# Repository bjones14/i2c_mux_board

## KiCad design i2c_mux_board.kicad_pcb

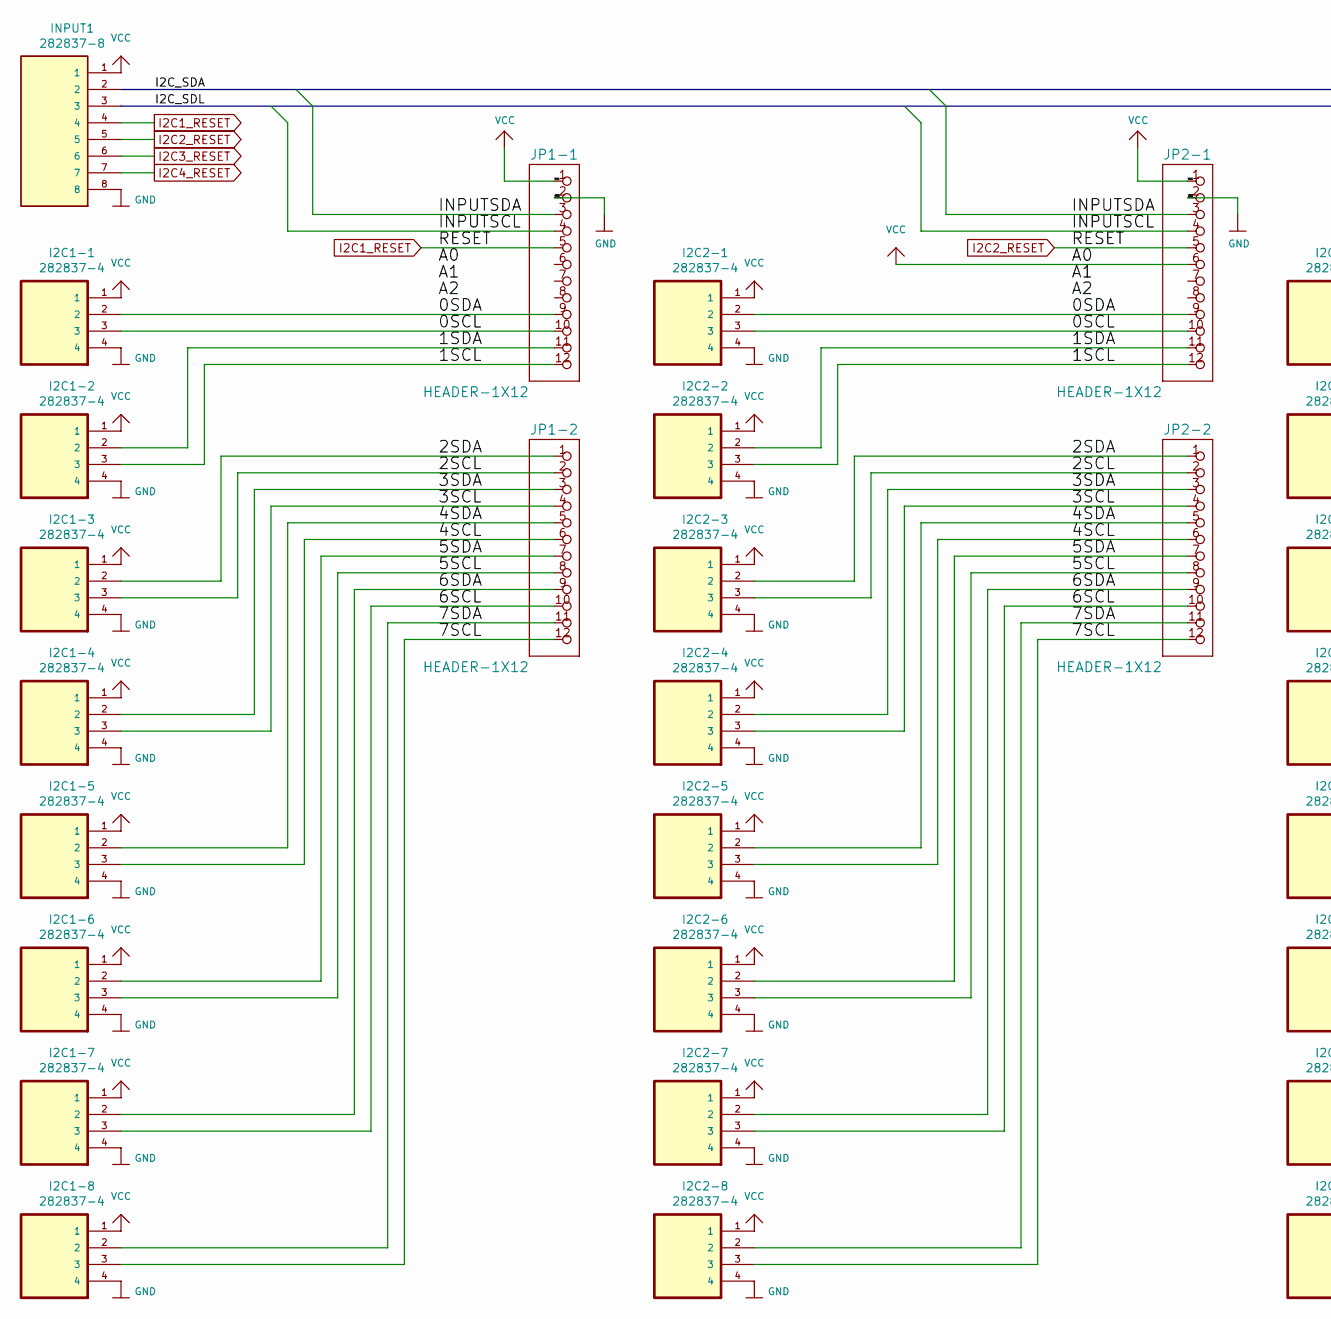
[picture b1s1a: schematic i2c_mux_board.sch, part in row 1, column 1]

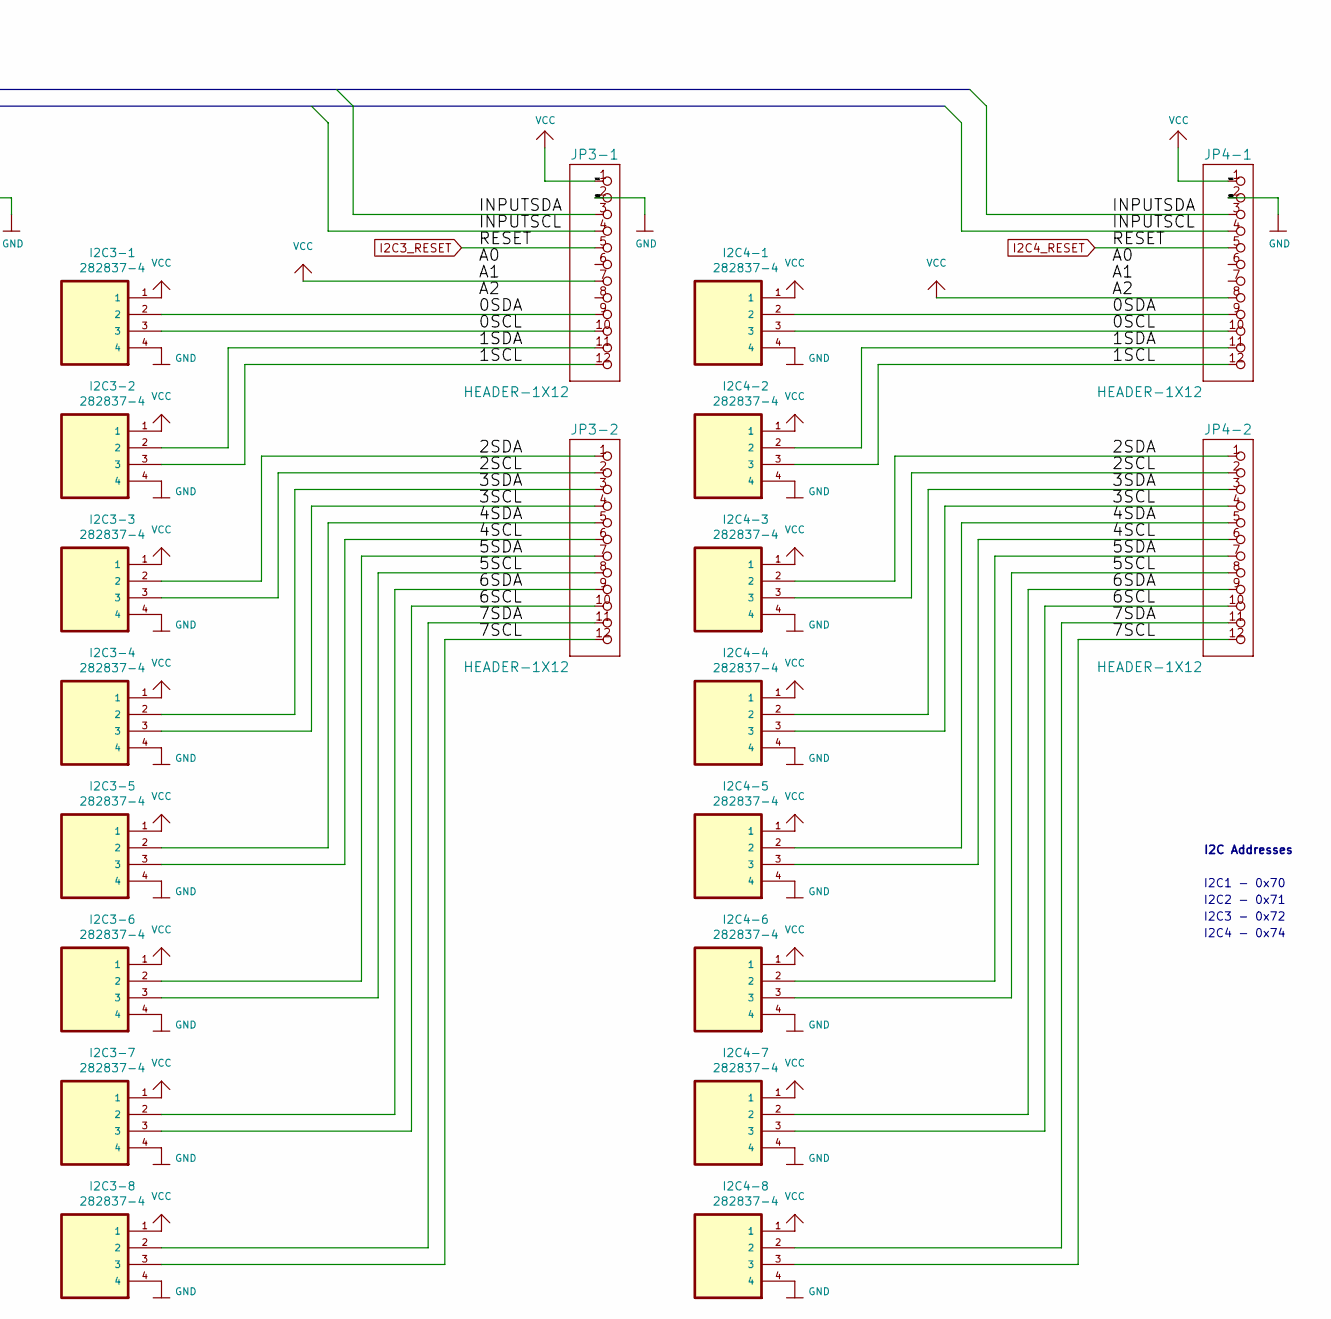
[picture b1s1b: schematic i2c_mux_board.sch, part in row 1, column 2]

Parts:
I2C1-1, I2C1-2, I2C1-3, I2C1-4, I2C1-5, I2C1-6, I2C1-7, I2C1-8, I2C2-1, I2C2-2, I2C2-3, I2C2-4, I2C2-5, I2C2-6, I2C2-7, I2C2-8, I2C3-1, I2C3-2, I2C3-3, I2C3-4, I2C3-5, I2C3-6, I2C3-7, I2C3-8, I2C4-1, I2C4-2, I2C4-3, I2C4-4, I2C4-5, I2C4-6, I2C4-7, I2C4-8: 282837-4; TE_282837-4; PARTREV G3
INPUT1: 282837-8; TE_282837-8; PARTREV H
JP1-1, JP1-2, JP2-1, JP2-2, JP3-1, JP3-2, JP4-1, JP4-2: HEADER-1X12; PinSocket_1x12_P2.54mm_Vertical

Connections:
/0SCL: I2C1-1.3, I2C2-1.3, I2C3-1.3, I2C4-1.3, JP1-1.10, JP2-1.10, JP3-1.10, JP4-1.10
/0SDA: I2C1-1.2, I2C2-1.2, I2C3-1.2, I2C4-1.2, JP1-1.9, JP2-1.9, JP3-1.9, JP4-1.9
/1SCL: I2C1-2.3, I2C2-2.3, I2C3-2.3, I2C4-2.3, JP1-1.12, JP2-1.12, JP3-1.12, JP4-1.12
/1SDA: I2C1-2.2, I2C2-2.2, I2C3-2.2, I2C4-2.2, JP1-1.11, JP2-1.11, JP3-1.11, JP4-1.11
/2SCL: I2C1-3.3, I2C2-3.3, I2C3-3.3, I2C4-3.3, JP1-2.2, JP2-2.2, JP3-2.2, JP4-2.2
/2SDA: I2C1-3.2, I2C2-3.2, I2C3-3.2, I2C4-3.2, JP1-2.1, JP2-2.1, JP3-2.1, JP4-2.1
/3SCL: I2C1-4.3, I2C2-4.3, I2C3-4.3, I2C4-4.3, JP1-2.4, JP2-2.4, JP3-2.4, JP4-2.4
/3SDA: I2C1-4.2, I2C2-4.2, I2C3-4.2, I2C4-4.2, JP1-2.3, JP2-2.3, JP3-2.3, JP4-2.3
/4SCL: I2C1-5.3, I2C2-5.3, I2C3-5.3, I2C4-5.3, JP1-2.6, JP2-2.6, JP3-2.6, JP4-2.6
/4SDA: I2C1-5.2, I2C2-5.2, I2C3-5.2, I2C4-5.2, JP1-2.5, JP2-2.5, JP3-2.5, JP4-2.5
/5SCL: I2C1-6.3, I2C2-6.3, I2C3-6.3, I2C4-6.3, JP1-2.8, JP2-2.8, JP3-2.8, JP4-2.8
/5SDA: I2C1-6.2, I2C2-6.2, I2C3-6.2, I2C4-6.2, JP1-2.7, JP2-2.7, JP3-2.7, JP4-2.7
/6SCL: I2C1-7.3, I2C2-7.3, I2C3-7.3, I2C4-7.3, JP1-2.10, JP2-2.10, JP3-2.10, JP4-2.10
/6SDA: I2C1-7.2, I2C2-7.2, I2C3-7.2, I2C4-7.2, JP1-2.9, JP2-2.9, JP3-2.9, JP4-2.9
/7SCL: I2C1-8.3, I2C2-8.3, I2C3-8.3, I2C4-8.3, JP1-2.12, JP2-2.12, JP3-2.12, JP4-2.12
/7SDA: I2C1-8.2, I2C2-8.2, I2C3-8.2, I2C4-8.2, JP1-2.11, JP2-2.11, JP3-2.11, JP4-2.11
/INPUTSCL: JP1-1.4, JP2-1.4, JP3-1.4, JP4-1.4
/INPUTSDA: JP1-1.3, JP2-1.3, JP3-1.3, JP4-1.3
GND: I2C1-1.4, I2C1-2.4, I2C1-3.4, I2C1-4.4, I2C1-5.4, I2C1-6.4, I2C1-7.4, I2C1-8.4, I2C2-1.4, I2C2-2.4, I2C2-3.4, I2C2-4.4, I2C2-5.4, I2C2-6.4, I2C2-7.4, I2C2-8.4, I2C3-1.4, I2C3-2.4, I2C3-3.4, I2C3-4.4, I2C3-5.4, I2C3-6.4, I2C3-7.4, I2C3-8.4, I2C4-1.4, I2C4-2.4, I2C4-3.4, I2C4-4.4, I2C4-5.4, I2C4-6.4, I2C4-7.4, I2C4-8.4, INPUT1.8, JP1-1.2, JP2-1.2, JP3-1.2, JP4-1.2
I2C1_RESET: INPUT1.4, INPUT1.5, INPUT1.6, INPUT1.7, JP1-1.5, JP2-1.5, JP3-1.5, JP4-1.5
VCC: I2C1-1.1, I2C1-2.1, I2C1-3.1, I2C1-4.1, I2C1-5.1, I2C1-6.1, I2C1-7.1, I2C1-8.1, I2C2-1.1, I2C2-2.1, I2C2-3.1, I2C2-4.1, I2C2-5.1, I2C2-6.1, I2C2-7.1, I2C2-8.1, I2C3-1.1, I2C3-2.1, I2C3-3.1, I2C3-4.1, I2C3-5.1, I2C3-6.1, I2C3-7.1, I2C3-8.1, I2C4-1.1, I2C4-2.1, I2C4-3.1, I2C4-4.1, I2C4-5.1, I2C4-6.1, I2C4-7.1, I2C4-8.1, INPUT1.1, JP1-1.1, JP2-1.1, JP2-1.6, JP3-1.1, JP3-1.7, JP4-1.1, JP4-1.8

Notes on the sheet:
I2C Addresses
I2C1 - 0x70
I2C2 - 0x71
I2C3 - 0x72
I2C4 - 0x74

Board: 2 copper layers, 41 parts (0 on the bottom side), 21 nets, no tracks yet.

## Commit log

2021-07-27 initial commit of kicad design files
